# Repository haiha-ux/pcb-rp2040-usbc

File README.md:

# RP2040 USB-C board, 4 layers, with a 2x2 production panel

Owner: Ha Phan Thanh Hai (GitHub `haiha-ux`). A small RP2040 development board in KiCad 10, laid out for the JLCPCB 4-layer stackup JLC04161H-7628, with fabrication and assembly files and a 2x2 panel. The board is 30 × 58 mm and has a USB-C device port, 16 MB QSPI flash, a 3.3 V LDO, BOOTSEL and RESET buttons, a 3-pin SWD header, a status LED on GPIO25 and two 1x20 headers that bring out GPIO0 to GPIO29.

The board has not been manufactured or tested. Everything below was checked with KiCad's ERC and DRC and with the scripts in `tools/`.

| Schematic | Top copper | Bottom copper |
|---|---|---|
|  |  |  |

| 3D view | 2x2 panel |
|---|---|
|  |  |

## Files

| Path | Content |
|---|---|
| `rp2040_usbc.kicad_sch`, `rp2040_usbc.kicad_pcb`, `rp2040_usbc.kicad_pro` | KiCad 10 project |
| `rp2040_usbc_schematic.pdf` | schematic |
| `fab/gerber/`, `fab/rp2040_usbc-gerber.zip` | Gerber X2 for 4 copper layers, mask, paste, silk, outline; Excellon drill (PTH and NPTH separate) |
| `fab/rp2040_usbc-BOM.csv` | BOM with manufacturer, MPN and LCSC part number for every line |
| `fab/rp2040_usbc-CPL.csv` | pick-and-place file with JLC column names |
| `panel/rp2040_usbc_panel.kicad_pcb`, `panel/rp2040_usbc_panel-gerber.zip` | 2x2 panel and its Gerber/drill set |
| `reports/` | ERC and DRC reports for the board, DRC for the panel, measured fab minimums |
| `tools/` | the scripts that built and checked all of the above |

## Circuit

The circuit follows the minimal design in section 2 of Raspberry Pi's "Hardware design with RP2040": W25Q128JVS QSPI flash, ABM8-272-T3 12 MHz crystal with 15 pF load capacitors and a 1 kΩ series resistor on XOUT, 27 Ω series resistors on USB D+ and D- close to the chip, 1 µF on VREG_VIN and VREG_VOUT and 100 nF on each IOVDD and DVDD pin. RUN has no internal pull-up on the RP2040, so it gets 10 kΩ to 3.3 V and the RESET button pulls it low. BOOTSEL pulls QSPI_SS low through 1 kΩ.

Some parts differ from the reference. The regulator is an AP2112K-3.3 in SOT-23-5 instead of the NCP1117, which keeps it clear of the header rows. USB uses a USB-C receptacle wired as a sink, with 5.1 kΩ from each CC pin to ground, and both D+/D- pin pairs of the receptacle are joined so the plug works either way round. A USBLC6-2SC6 protects D+, D- and VBUS. The RP2040 is a USB Full-Speed device (12 Mbit/s).

ERC reports 0 errors and 0 warnings. `tools/check_netlist.py` exports the netlist with kicad-cli and compares all 54 designed nets pin by pin with the net table in `tools/design.py`. It matches completely, and the script also checks itself by moving one pin and confirming that the comparison then fails.

## Stackup and USB impedance

The stackup is JLC04161H-7628 from the JLCPCB impedance page (https://jlcpcb.com/impedance): 35 µm outer copper, 0.2104 mm of 7628 prepreg (Er 4.4) to the first inner layer, a 1.065 mm core and 15.2 µm inner copper. The layers are used as signals and ground pour on F.Cu, a solid ground plane on In1, a 3.3 V pour on In2, and signals and ground pour on B.Cu. The USB pair on F.Cu therefore runs over an unbroken ground plane on In1.

For 90 Ω differential impedance the pair is 0.27 mm wide with a 0.15 mm gap. `tools/usb_impedance.py` computes this with the Hammerstad-Jensen microstrip model (scikit-rf) and the IPC-2141 coupling term. The two single-ended models agree within 2 %, and the result is 90.0 Ω. The tracks neck down to 0.20 mm only at the last fraction of a millimetre into the pads of the 0402 resistors and the QFN.

The USB lines are routed by hand in `tools/build_pcb.py`, from the receptacle through the ESD diode and the 27 Ω resistors to pins 46 and 47. D+ is 17.6 mm long and D- is 18.1 mm. The 0.5 mm difference is far below anything that matters at Full Speed. D+ uses two vias to join the receptacle's second D+ pin from underneath, and D- needs none.

## Layout and routing

Placement and the critical routing are done in Python with KiCad's pcbnew API. The decoupling capacitors sit next to their supply pins as in figure 6 of the Raspberry Pi guide, with the 1.1 V and 3.3 V pins fanned out by hand. The remaining signals were routed by Freerouting 2.4.1, with the USB pair and the hand-made fanout locked so the router could not move them. After routing the script adds ground stitching vias on a 2.5 mm grid wherever they keep 0.5 mm from other copper, then fills the pours. The board has 146 vias, all 0.40 mm with a 0.20 mm drill.

DRC with schematic parity reports 0 errors, 0 unconnected pads and 0 parity problems. Two warnings remain, both for the USB-C receptacle's silkscreen at the board edge. The receptacle is meant to sit flush with the edge, so I left them.

The references of 10 small parts (C3, C7, C8, C10, C12, C15, C17, R3, R4 and U3) did not fit on the silkscreen at JLCPCB's minimum text size of 1.0 mm without touching pads, so they are on the F.Fab layer. They still appear in the assembly drawing and in the CPL file.

## Panel

`tools/panelize.py` builds a 2x2 panel of 76 × 132 mm. The boards are separated by 2 mm routed slots and surrounded by 5 mm rails. Each rail corner has a 2 mm tooling hole, and there are three 1 mm fiducials, all centred 3.85 mm from the panel edge as JLCPCB asks. The boards hang on 5 mm breakaway tabs with mouse bites, which are six 0.5 mm holes at 0.8 mm pitch (0.3 mm of material between holes). Each board has two tabs on each long side, and the bottom row also has two tabs to the bottom rail.

There are no tabs on the top edge of a board, because that edge carries the USB-C receptacle and two M2 mounting holes. A tab there would put mouse-bite holes inside the mounting hole courtyards, and a broken tab would leave a rough edge next to the connector. The receptacle body reaches 0.05 mm past the board edge and its courtyard 0.53 mm, so it stays inside the 2 mm slot.

The four copies share net names, so the panel DRC also lists every net as unconnected between copies. `tools/check_panel.py` separates these. It finds 0 unconnected items inside any one board, and 171 links between copies, which is 57 nets × 3. The only violations are the same USB-C silkscreen warnings, 8 in total.

## DFM check against JLCPCB capabilities

The board values come from `tools/dfm_measure.py` (`reports/dfm_measure.json`). The limits are from https://jlcpcb.com/capabilities/pcb-capabilities.

| Item | This design | JLCPCB limit |
|---|---|---|
| Track width (multilayer) | 0.15 mm minimum, 0.27 mm USB | 0.09 mm |
| Copper clearance | 0.15 mm rule | 0.09 mm |
| Via | 0.40 mm pad, 0.20 mm drill | 0.25 mm pad, 0.15 mm drill |
| Hole to hole | 0.36 mm minimum | 0.2 mm |
| Copper to routed edge | 0.5 mm rule, nearest track 1.73 mm | 0.2 mm |
| Solder mask between QFN pads | 0.2 mm (0.4 mm pitch, 0.2 mm pads, no expansion) | 0.1 mm |
| Silkscreen text | 1.0 mm high, 0.15 mm stroke | 1.0 mm, 0.15 mm |
| Panel rails, tooling holes, fiducials | 5 mm, 2 mm, 1 mm at 3.85 mm | 5 mm, 2 mm, 1 mm at 3.85 mm |
| Breakaway tab | 5 mm wide | 5 mm or more with mouse bites |
| Mouse bites | 0.5 mm holes, 0.3 mm apart | 0.5 to 0.8 mm holes, 0.2 to 0.3 mm apart |

## Limitations

- The 90 Ω figure comes from closed-form formulas, which are good to roughly ±10 %. I did not run a field solver. For a controlled-impedance order, the trace width should be confirmed with JLCPCB's own calculator, or the impedance control option selected so the fab adjusts it.
- The pair is not coupled for its whole length. It splits at the receptacle's two pin rows, at the ESD diode and at the series resistors. That is acceptable for Full-Speed USB but would not be for High-Speed.
- The CPL rotations are KiCad's. JLCPCB often needs some parts (QFN, SOT-23, the USB-C receptacle) rotated in its placement preview, so check them there before ordering assembly.
- Freerouting does not give the same result twice. `build_pcb.py` repeats the routing until DRC is clean, so a rebuild gives a valid board but not necessarily the same track shapes.
- The panel uses mouse-bite tabs only. I did not evaluate a V-score version, which would leave cleaner edges but needs straight cuts across the whole panel and copper kept at least 0.4 mm from each cut.

## Rebuild

```bash
python tools/build_schematic.py                       # schematic through Konnect (KONNECT_EXE)
python tools/check_netlist.py
"<KiCad>/bin/python.exe" tools/build_pcb.py clean     # placement, USB + fanout, Freerouting (JAVA, FREEROUTING_JAR)
"<KiCad>/bin/python.exe" tools/build_pcb.py silk
"<KiCad>/bin/python.exe" tools/panelize.py
"<KiCad>/bin/python.exe" tools/check_panel.py
"<KiCad>/bin/python.exe" tools/dfm_measure.py
bash tools/export_outputs.sh                          # reports, Gerber, drill, BOM, CPL, renders, panel Gerber
```

Requires KiCad 10, Python 3.11 with scikit-rf, PyMuPDF and cairosvg, Freerouting 2.4.1 on Java 21 or newer, and the Konnect KiCad plugin for the schematic step.

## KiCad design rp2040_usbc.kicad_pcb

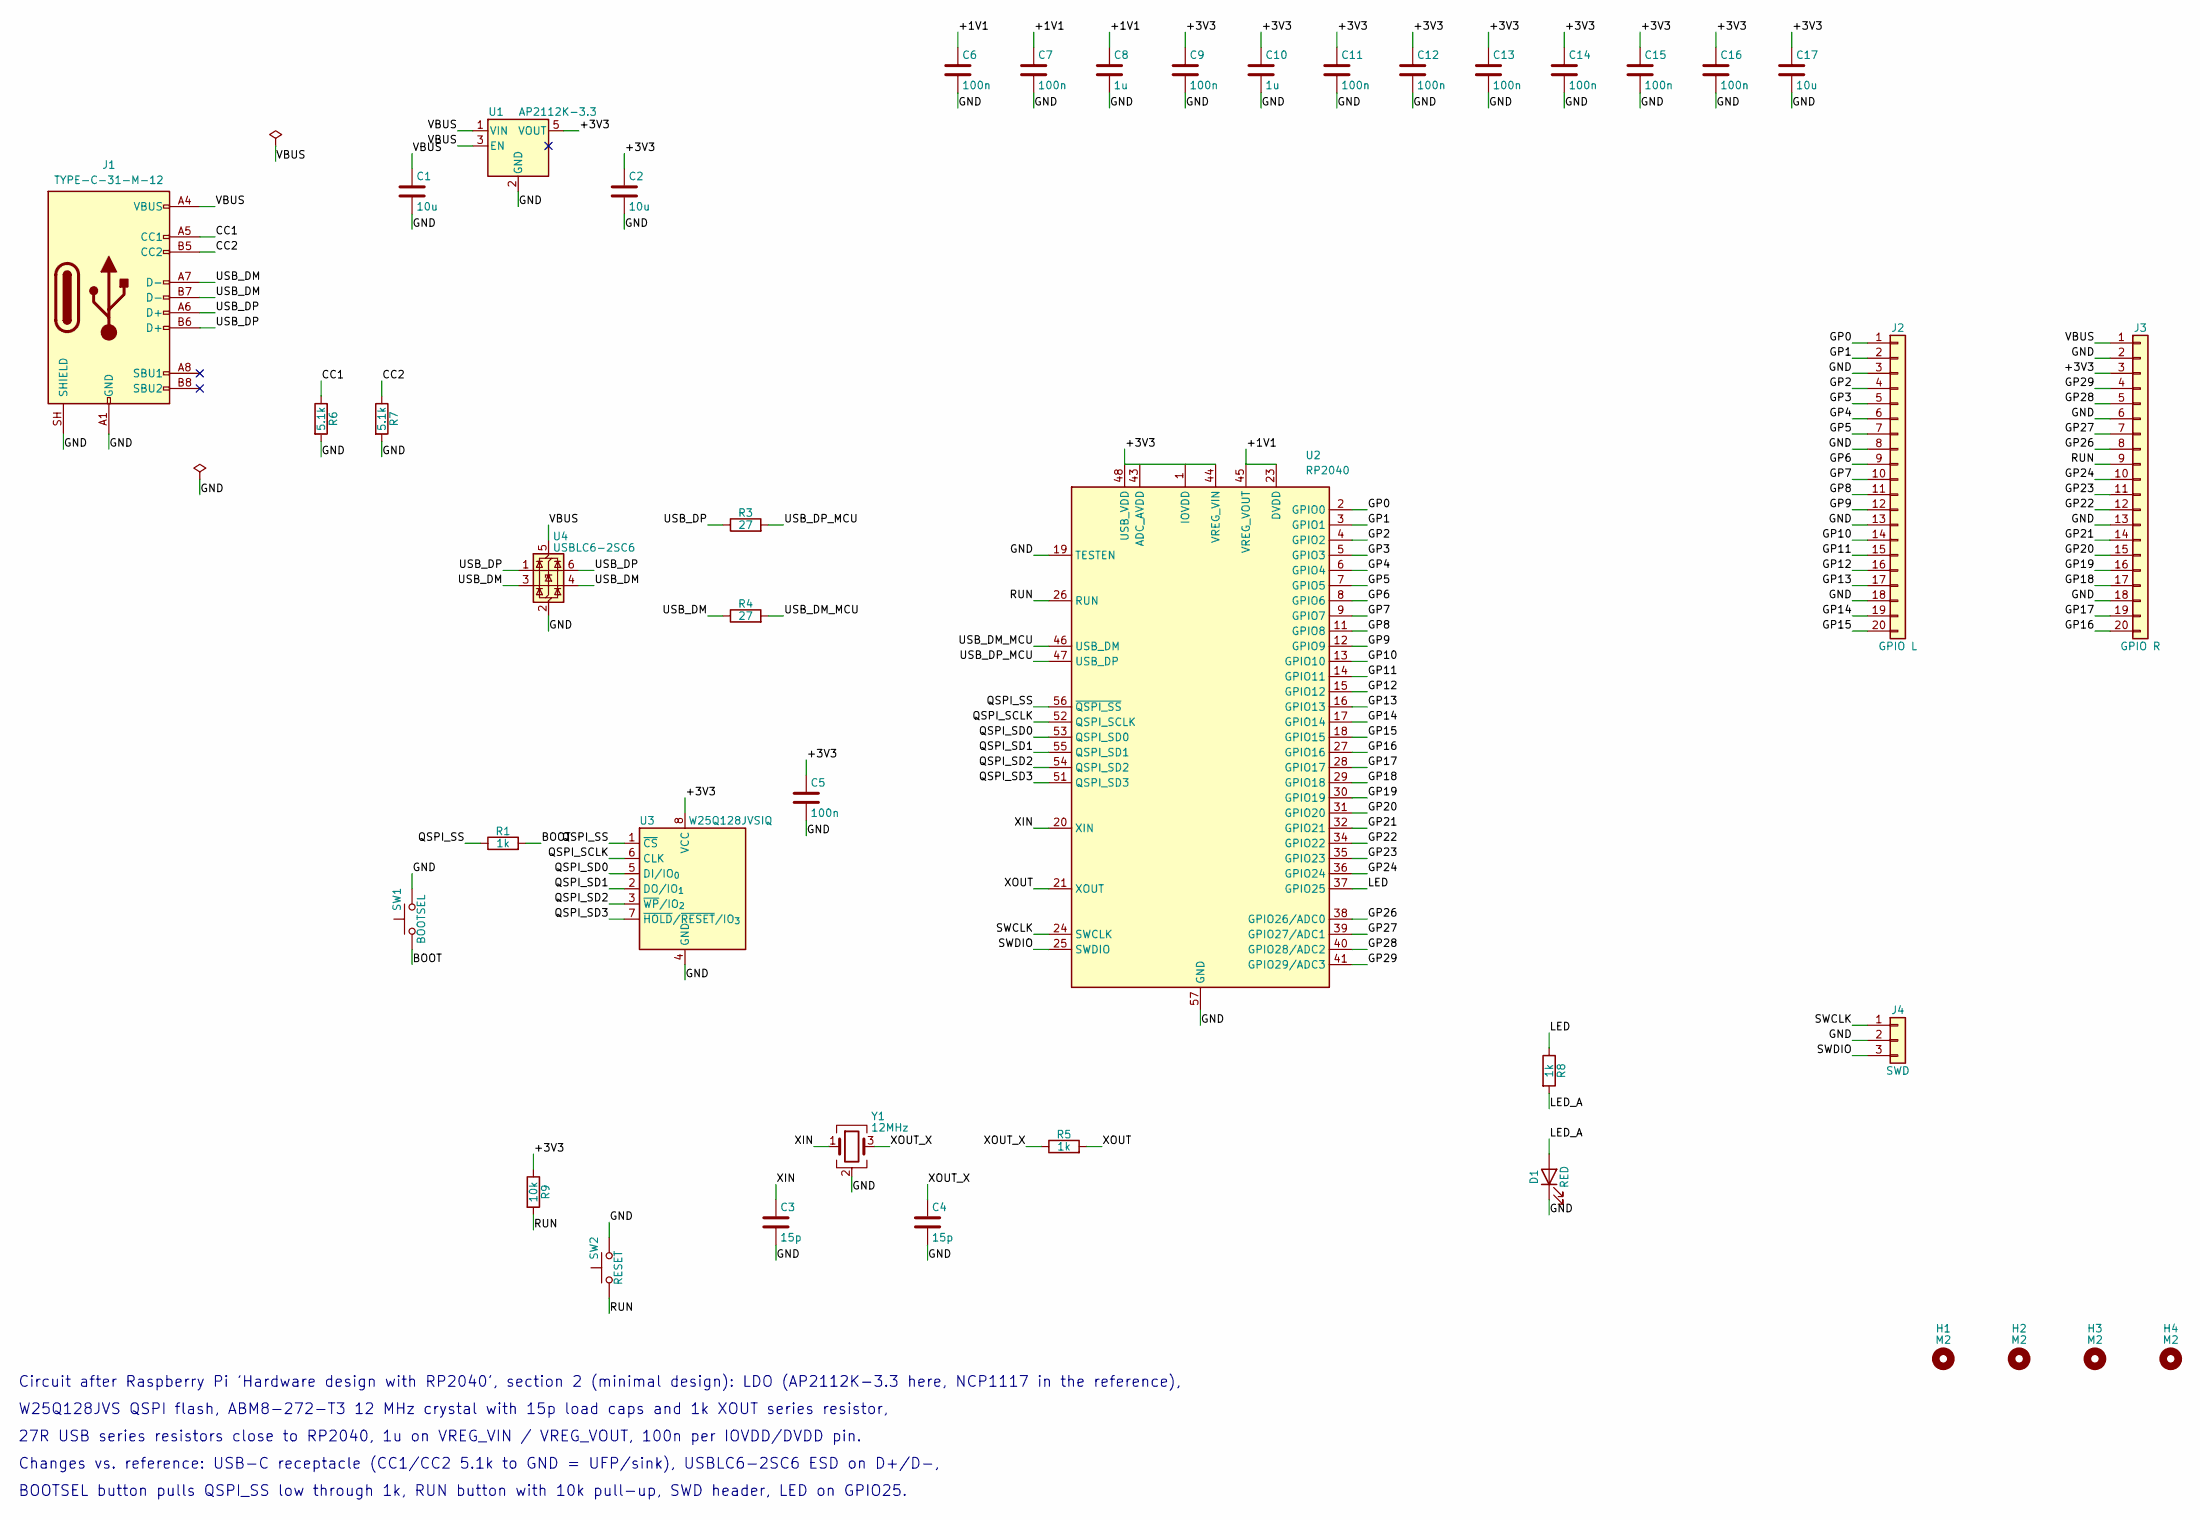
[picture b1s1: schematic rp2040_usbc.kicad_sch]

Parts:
C1, C2, C17: 10u; C_0805_2012Metric; MPN CL21A106KAYNNNE; LCSC C15850
C3, C4: 15p; C_0402_1005Metric; MPN 0402CG150J500NT; LCSC C1548
C5, C6, C7, C9, C11, C12, C13, C14, C15, C16: 100n; C_0402_1005Metric; MPN CL05B104KO5NNNC; LCSC C1525
C8, C10: 1u; C_0402_1005Metric; MPN CL05A105KA5NQNC; LCSC C52923
D1: RED; LED_0603_1608Metric; MPN KT-0603R; LCSC C2286
H1, H2, H3, H4: M2; MountingHole_2.2mm_M2
J1: TYPE-C-31-M-12; USB_C_Receptacle_HRO_TYPE-C-31-M-12; MPN TYPE-C-31-M-12; LCSC C165948
J2: GPIO L; PinHeader_1x20_P2.54mm_Vertical; MPN 2.54-1*20PStraight pin; LCSC C50981
J3: GPIO R; PinHeader_1x20_P2.54mm_Vertical; MPN 2.54-1*20PStraight pin; LCSC C50981
J4: SWD; PinHeader_1x03_P2.54mm_Vertical; MPN 22284030; LCSC C587036
R1, R5, R8: 1k; R_0402_1005Metric; MPN 0402WGF1001TCE; LCSC C11702
R3, R4: 27; R_0402_1005Metric; MPN FRC0402F27R0TS; LCSC C2909343
R6, R7: 5.1k; R_0402_1005Metric; MPN 0402WGF5101TCE; LCSC C25905
R9: 10k; R_0402_1005Metric; MPN 0402WGF1002TCE; LCSC C25744
SW1: BOOTSEL; SW_Push_1P1T_XKB_TS-1187A; MPN TS-1187A-B-A-B; LCSC C318884
SW2: RESET; SW_Push_1P1T_XKB_TS-1187A; MPN TS-1187A-B-A-B; LCSC C318884
U1: AP2112K-3.3; SOT-23-5; MPN AP2112K-3.3TRG1; LCSC C51118
U2: RP2040; QFN-56-1EP_7x7mm_P0.4mm_EP3.2x3.2mm; MPN RP2040; LCSC C2040
U3: W25Q128JVSIQ; SOIC-8_5.3x5.3mm_P1.27mm; MPN W25Q128JVSIQ; LCSC C97521
U4: USBLC6-2SC6; SOT-23-6; MPN USBLC6-2SC6; LCSC C7519
Y1: 12MHz; Crystal_SMD_3225-4Pin_3.2x2.5mm; MPN ABM8-272-T3; LCSC C20625731

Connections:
/+1V1: C6.1, C7.1, C8.1, U2.23 (DVDD), U2.45 (VREG_VOUT), U2.50 (DVDD)
/+3V3: C2.1, C5.1, C9.1, C10.1, C11.1, C12.1, C13.1, C14.1, C15.1, C16.1, C17.1, J3.3, R9.1, U1.5 (VOUT), U2.1 (IOVDD), U2.10 (IOVDD), U2.22 (IOVDD), U2.33 (IOVDD), U2.42 (IOVDD), U2.43 (ADC_AVDD), U2.44 (VREG_VIN), U2.48 (USB_VDD), U2.49 (IOVDD), U3.8 (VCC)
/BOOT: R1.2, SW1.1
/CC1: J1.A5 (CC1), R6.1
/CC2: J1.B5 (CC2), R7.1
/GND: C1.2, C2.2, C3.2, C4.2, C5.2, C6.2, C7.2, C8.2, C9.2, C10.2, C11.2, C12.2, C13.2, C14.2, C15.2, C16.2, C17.2, D1.1 (K), J1.A1 (GND), J1.A12 (GND), J1.B1 (GND), J1.B12 (GND), J1.SH (SHIELD), J2.3, J2.8, J2.13, J2.18, J3.2, J3.6, J3.13, J3.18, J4.2, R6.2, R7.2, SW1.2, SW2.2, U1.2 (GND), U2.19 (TESTEN), U2.57 (GND), U3.4 (GND), U4.2 (GND), Y1.2 (G), Y1.4 (G)
/GP0: J2.1, U2.2 (GPIO0)
/GP1: J2.2, U2.3 (GPIO1)
/GP2: J2.4, U2.4 (GPIO2)
/GP3: J2.5, U2.5 (GPIO3)
/GP4: J2.6, U2.6 (GPIO4)
/GP5: J2.7, U2.7 (GPIO5)
/GP6: J2.9, U2.8 (GPIO6)
/GP7: J2.10, U2.9 (GPIO7)
/GP8: J2.11, U2.11 (GPIO8)
/GP9: J2.12, U2.12 (GPIO9)
/GP10: J2.14, U2.13 (GPIO10)
/GP11: J2.15, U2.14 (GPIO11)
/GP12: J2.16, U2.15 (GPIO12)
/GP13: J2.17, U2.16 (GPIO13)
/GP14: J2.19, U2.17 (GPIO14)
/GP15: J2.20, U2.18 (GPIO15)
/GP16: J3.20, U2.27 (GPIO16)
/GP17: J3.19, U2.28 (GPIO17)
/GP18: J3.17, U2.29 (GPIO18)
/GP19: J3.16, U2.30 (GPIO19)
/GP20: J3.15, U2.31 (GPIO20)
/GP21: J3.14, U2.32 (GPIO21)
/GP22: J3.12, U2.34 (GPIO22)
/GP23: J3.11, U2.35 (GPIO23)
/GP24: J3.10, U2.36 (GPIO24)
/GP26: J3.8, U2.38 (GPIO26/ADC0)
/GP27: J3.7, U2.39 (GPIO27/ADC1)
/GP28: J3.5, U2.40 (GPIO28/ADC2)
/GP29: J3.4, U2.41 (GPIO29/ADC3)
/LED: R8.1, U2.37 (GPIO25)
/LED_A: D1.2 (A), R8.2
/QSPI_SCLK: U2.52 (QSPI_SCLK), U3.6 (CLK)
/QSPI_SD0: U2.53 (QSPI_SD0), U3.5 (DI/IO_{0})
/QSPI_SD1: U2.55 (QSPI_SD1), U3.2 (DO/IO_{1})
/QSPI_SD2: U2.54 (QSPI_SD2), U3.3 (~WP/IO_{2})
/QSPI_SD3: U2.51 (QSPI_SD3), U3.7 (~HOLD/~RESET/IO_{3})
/QSPI_SS: R1.1, U2.56 (~QSPI_SS), U3.1 (~CS)
/RUN: J3.9, R9.2, SW2.1, U2.26 (RUN)
/SWCLK: J4.1, U2.24 (SWCLK)
/SWDIO: J4.3, U2.25 (SWDIO)
/USB_DM: J1.A7 (D-), J1.B7 (D-), R4.1, U4.3 (I/O2), U4.4 (I/O2)
/USB_DM_MCU: R4.2, U2.46 (USB_DM)
/USB_DP: J1.A6 (D+), J1.B6 (D+), R3.1, U4.1 (I/O1), U4.6 (I/O1)
/USB_DP_MCU: R3.2, U2.47 (USB_DP)
/VBUS: C1.1, J1.A4 (VBUS), J1.A9 (VBUS), J1.B4 (VBUS), J1.B9 (VBUS), J3.1, U1.1 (VIN), U1.3 (EN), U4.5 (VBUS)
/XIN: C3.1, U2.20 (XIN), Y1.1
/XOUT: R5.2, U2.21 (XOUT)
/XOUT_X: C4.1, R5.1, Y1.3

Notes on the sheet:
Circuit after Raspberry Pi 'Hardware design with RP2040', section 2 (minimal design): LDO (AP2112K-3.3 here, NCP1117 in the reference),
W25Q128JVS QSPI flash, ABM8-272-T3 12 MHz crystal with 15p load caps and 1k XOUT series resistor,
27R USB series resistors close to RP2040, 1u on VREG_VIN / VREG_VOUT, 100n per IOVDD/DVDD pin.
Changes vs. reference: USB-C receptacle (CC1/CC2 5.1k to GND = UFP/sink), USBLC6-2SC6 ESD on D+/D-,
BOOTSEL button pulls QSPI_SS low through 1k, RUN button with 10k pull-up, SWD header, LED on GPIO25.

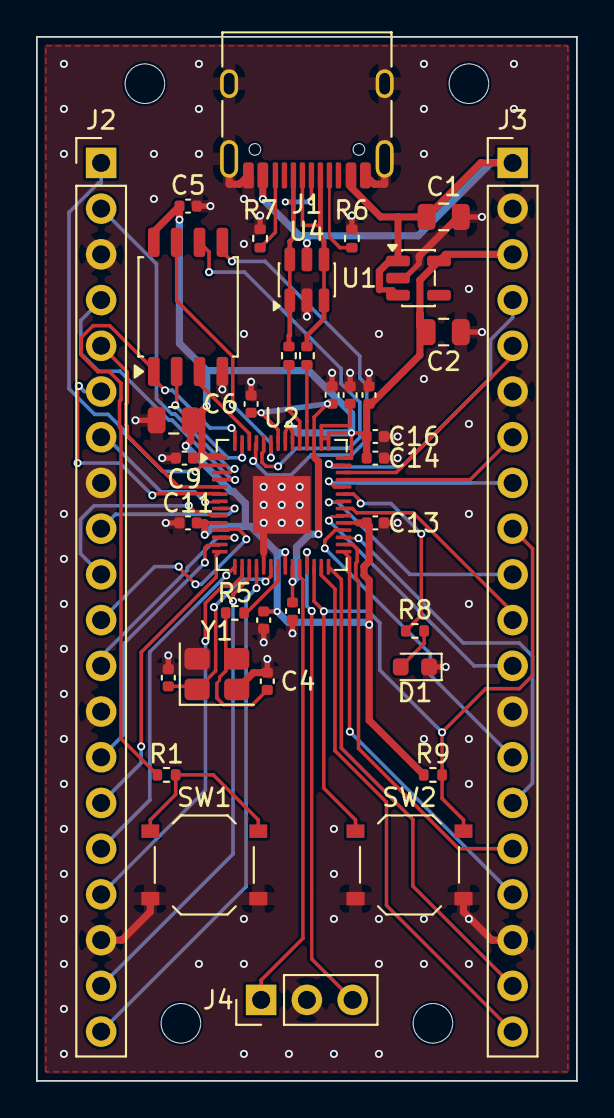
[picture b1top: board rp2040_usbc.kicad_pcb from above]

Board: 4 copper layers, 30.0 x 58.0 mm, 41 parts (0 on the bottom side), 54 nets.

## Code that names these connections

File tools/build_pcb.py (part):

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    center(b, "C8", 16.4, 19.9, 90)     # VREG_VOUT 45 (1u), hand-routed
    center(b, "C6", 11.9, 20.4, 90)     # DVDD 50
    center(b, "C15", 18.45, 19.9, 90)    # IOVDD 49 / USB_VDD 48
    # crystal below XIN/XOUT (pins 20/21)
    center(b, "Y1", 10.0, 35.4, 0)
    center(b, "C3", 7.3, 35.6, 90)
    center(b, "C4", 12.8, 35.8, 90)
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    track(b, [gnd, (gnd[0], gnd[1] + 0.9)], "/GND", F, 0.3)
    via(b, gnd[0], gnd[1] + 0.9, "/GND")
    # ESD -> 27R series resistors -> RP2040 USB_DP (47) / USB_DM (46)
    for bot, r, pin, net_a, net_b in ((bot_dp, "R3", "47", "/USB_DP", "/USB_DP_MCU"),
                                      (bot_dm, "R4", "46", "/USB_DM", "/USB_DM_MCU")):
        r1, r2, ip = P(b, r, "1"), P(b, r, "2"), P(b, "U2", pin)
        dx = abs(r1[0] - bot[0])
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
